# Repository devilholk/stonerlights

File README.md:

stonerlights
============

This project aims to control a bunch of (so far) local RGB LED's and other LED related devices.

This project is recently started and it puzzled together from old learning experiences so for now the structure is not the best.
Some parts may have separate licenses, I have not yet examined those legal details, if this applies it is stated in those files.

Be patient

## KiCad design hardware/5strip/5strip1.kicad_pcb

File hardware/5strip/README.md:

== Att göra ==

* Fixa till kretskortet så det uppfyller följande kriterier
** Klarar massa ström
** Har tillräckligt med C
** Kan prata RS-485 i halv duplex
** Kan prata USB
** Kan monitora matningsspänning som kan vara separat från 12 volt ifall en extern switch används

* Om tid finnes
** Stöd för kondensatormikrofron

== Notera ==

Förmodligen kommer man bara kunna använda en UART, kanske måste göra något fiffigt för att kunna använda båda vettigt, t.ex. multiplexa UART.

Detta dokumentet är ihophaffsat.

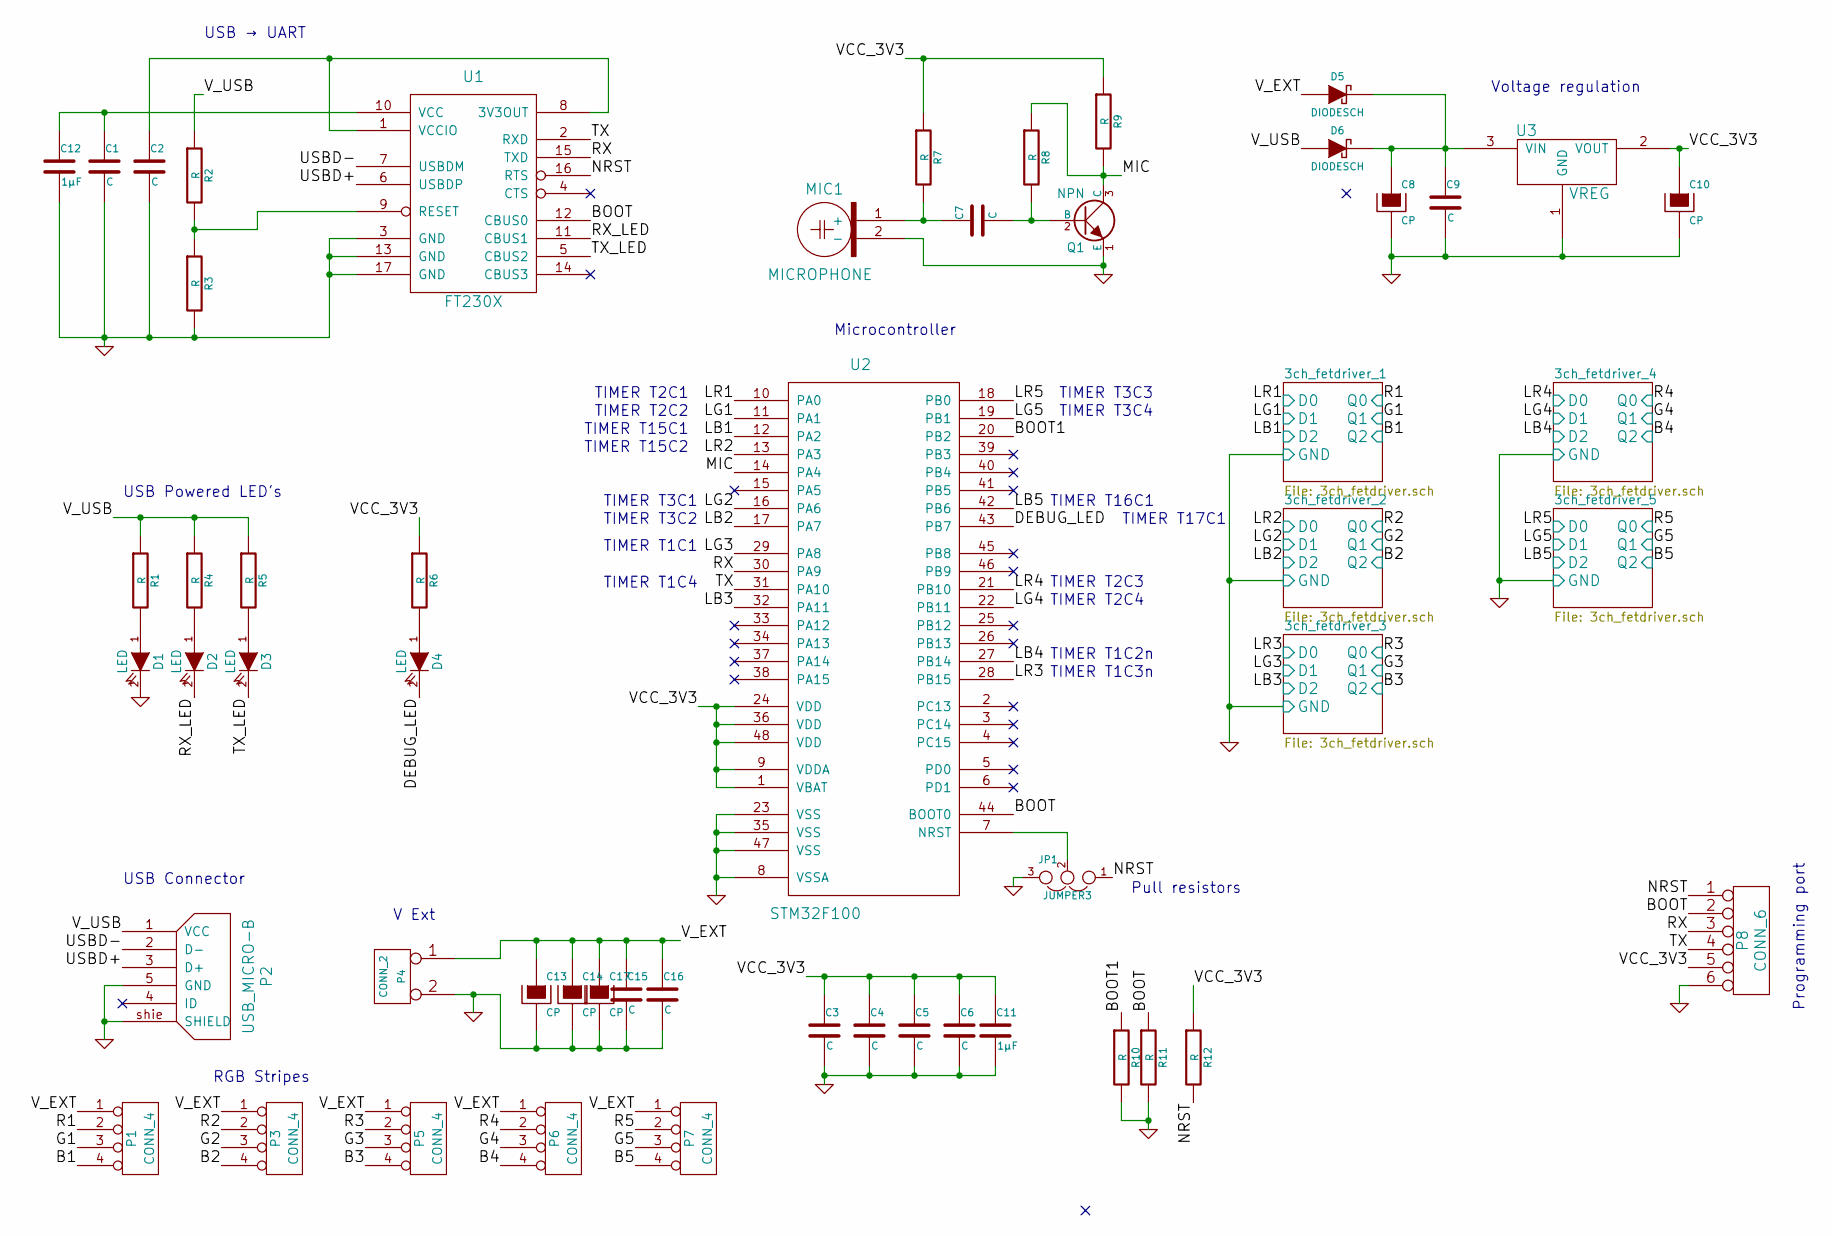
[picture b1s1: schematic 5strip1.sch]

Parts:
C1, C2, C3, C4, C5, C6, C7, C9, C15, C16: C
C8, C10, C13, C14, C17: CP
C11, C12: 1µF
D1, D2, D3, D4: LED
D5, D6: DIODESCH
JP1: JUMPER3
MIC1: MICROPHONE
P1, P3, P5, P6, P7: CONN_4
P2: USB_MICRO-B
P4: CONN_2
P8: CONN_6
Q1: NPN
R1, R2, R3, R4, R5, R6, R7, R8, R9, R10, R11, R12: R
U1: FT230X
U2: STM32F100
U3: VREG

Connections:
/3ch_fetdriver_1/D0: U2.10 (PA0); also elsewhere on the board
/3ch_fetdriver_1/D1: U2.11 (PA1); also elsewhere on the board
/3ch_fetdriver_1/D2: U2.12 (PA2); also elsewhere on the board
/3ch_fetdriver_1/Q0: P1.2; also elsewhere on the board
/3ch_fetdriver_1/Q1: P1.3; also elsewhere on the board
/3ch_fetdriver_1/Q2: P1.4; also elsewhere on the board
/3ch_fetdriver_2/D0: U2.13 (PA3); also elsewhere on the board
/3ch_fetdriver_2/D1: U2.16 (PA6); also elsewhere on the board
/3ch_fetdriver_2/D2: U2.17 (PA7); also elsewhere on the board
/3ch_fetdriver_2/Q0: P3.2; also elsewhere on the board
/3ch_fetdriver_2/Q1: P3.3; also elsewhere on the board
/3ch_fetdriver_2/Q2: P3.4; also elsewhere on the board
/3ch_fetdriver_3/D0: U2.28 (PB15); also elsewhere on the board
/3ch_fetdriver_3/D1: U2.29 (PA8); also elsewhere on the board
/3ch_fetdriver_3/D2: U2.32 (PA11); also elsewhere on the board
/3ch_fetdriver_3/Q0: P5.2; also elsewhere on the board
/3ch_fetdriver_3/Q1: P5.3; also elsewhere on the board
/3ch_fetdriver_3/Q2: P5.4; also elsewhere on the board
/3ch_fetdriver_4/D0: U2.21 (PB10); also elsewhere on the board
/3ch_fetdriver_4/D1: U2.22 (PB11); also elsewhere on the board
/3ch_fetdriver_4/D2: U2.27 (PB14); also elsewhere on the board
/3ch_fetdriver_4/Q0: P6.2; also elsewhere on the board
/3ch_fetdriver_4/Q1: P6.3; also elsewhere on the board
/3ch_fetdriver_4/Q2: P6.4; also elsewhere on the board
/3ch_fetdriver_5/D0: U2.18 (PB0); also elsewhere on the board
/3ch_fetdriver_5/D1: U2.19 (PB1); also elsewhere on the board
/3ch_fetdriver_5/D2: U2.42 (PB6); also elsewhere on the board
/3ch_fetdriver_5/Q0: P7.2; also elsewhere on the board
/3ch_fetdriver_5/Q1: P7.3; also elsewhere on the board
/3ch_fetdriver_5/Q2: P7.4; also elsewhere on the board
/BOOT: P8.2, R11.1, U1.12 (CBUS0), U2.44 (BOOT0)
/BOOT1: R10.1, U2.20 (PB2)
/DEBUG_LED: D4.2 (K), U2.43 (PB7)
/MIC: Q1.3 (C), R8.1, R9.2, U2.14 (PA4)
/NRST: JP1.1, P8.1, R12.2, U1.16 (RTS)
/RX: P8.3, U1.15 (TXD), U2.30 (PA9)
/RX_LED: D2.2 (K), U1.11 (CBUS1)
/TX: P8.4, U1.2 (RXD), U2.31 (PA10)
/TX_LED: D3.2 (K), U1.5 (CBUS2)
/USBD+: P2.3 (D+), U1.6 (USBDP)
/USBD-: P2.2 (D-), U1.7 (USBDM)
/VCC_3V3: C3.1, C4.1, C5.1, C6.1, C10.1, C11.1, P8.5, R6.1, R7.1, R9.1, R12.1, U2.1 (VBAT), U2.9 (VDDA), U2.24 (VDD), U2.36 (VDD), U2.48 (VDD), U3.2 (VOUT), U3.4
/V_EXT: C13.1, C14.1, C15.1, C16.1, C17.1, D5.1 (A), P1.1, P3.1, P4.1, P5.1, P6.1, P7.1
/V_USB: D6.1 (A), P2.1 (VCC), R1.1, R2.1, R4.1, R5.1
GND: C1.2, C2.2, C3.2, C4.2, C5.2, C6.2, C8.2, C9.2, C10.2, C11.2, C12.2, C13.2, C14.2, C15.2, C16.2, C17.2, D1.2 (K), JP1.3, MIC1.2 (-), P2.5 (GND), P2.shie (SHIELD), P4.2 (PM), P8.6, Q1.1 (E), R3.2, R10.2, R11.2, U1.3 (GND), U1.13 (GND), U1.17 (GND), U2.8 (VSSA), U2.23 (VSS), U2.35 (VSS), U2.47 (VSS), U3.1 (GND); also elsewhere on the board
unnamed: C2.1, U1.1 (VCCIO), U1.8 (3V3OUT)
unnamed: JP1.2, U2.7 (NRST)
unnamed: R2.2, R3.1, U1.9 (RESET)
unnamed: C1.1, C12.1, U1.10 (VCC)
unnamed: C8.1, C9.1, D5.2 (K), D6.2 (K), U3.3 (VIN)
unnamed: C7.2, Q1.2 (B), R8.2
unnamed: C7.1, MIC1.1 (+), R7.2
unnamed: D4.1 (A), R6.2
unnamed: D2.1 (A), R4.2
unnamed: D1.1 (A), R1.2
unnamed: D3.1 (A), R5.2

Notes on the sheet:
USB Powered LED's
Pull resistors
Voltage regulation
USB Connector
Microcontroller
USB → UART
RGB Stripes
Programming port
V Ext
TIMER T3C4
TIMER T3C3
TIMER T2C2
TIMER T2C3
TIMER T2C4
TIMER T3C1
TIMER T3C2
TIMER T1C3n
TIMER T1C2n
TIMER T1C4
TIMER T1C1
TIMER T2C1
TIMER T16C1
TIMER T17C1
TIMER T15C1
TIMER T15C2

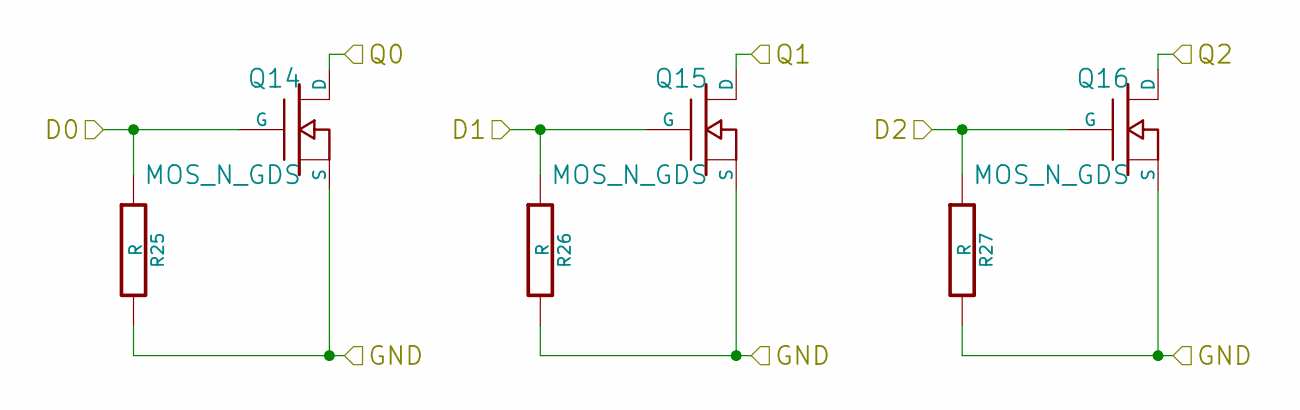
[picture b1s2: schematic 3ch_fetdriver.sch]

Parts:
Q2, Q3, Q4: MOS_N_GDS
R13, R14, R15: R

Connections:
/3ch_fetdriver_1/D0: Q2.1 (G), R13.1; also elsewhere on the board
/3ch_fetdriver_1/D1: Q3.1 (G), R14.1; also elsewhere on the board
/3ch_fetdriver_1/D2: Q4.1 (G), R15.1; also elsewhere on the board
/3ch_fetdriver_1/Q0: Q2.2 (D); also elsewhere on the board
/3ch_fetdriver_1/Q1: Q3.2 (D); also elsewhere on the board
/3ch_fetdriver_1/Q2: Q4.2 (D); also elsewhere on the board
GND: Q2.3 (S), Q3.3 (S), Q4.3 (S), R13.2, R14.2, R15.2; also elsewhere on the board

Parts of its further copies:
Q5, Q6, Q7, Q8, Q9, Q10, Q11, Q12, Q13, Q14, Q15, Q16: MOS_N_GDS
R16, R17, R18, R19, R20, R21, R22, R23, R24, R25, R26, R27: R

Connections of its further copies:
/3ch_fetdriver_2/D0: Q5.1 (G), R16.1; also elsewhere on the board
/3ch_fetdriver_2/D1: Q6.1 (G), R17.1; also elsewhere on the board
/3ch_fetdriver_2/D2: Q7.1 (G), R18.1; also elsewhere on the board
/3ch_fetdriver_2/Q0: Q5.2 (D); also elsewhere on the board
/3ch_fetdriver_2/Q1: Q6.2 (D); also elsewhere on the board
/3ch_fetdriver_2/Q2: Q7.2 (D); also elsewhere on the board
/3ch_fetdriver_3/D0: Q8.1 (G), R19.1; also elsewhere on the board
/3ch_fetdriver_3/D1: Q9.1 (G), R20.1; also elsewhere on the board
/3ch_fetdriver_3/D2: Q10.1 (G), R21.1; also elsewhere on the board
/3ch_fetdriver_3/Q0: Q8.2 (D); also elsewhere on the board
/3ch_fetdriver_3/Q1: Q9.2 (D); also elsewhere on the board
/3ch_fetdriver_3/Q2: Q10.2 (D); also elsewhere on the board
/3ch_fetdriver_4/D0: Q11.1 (G), R22.1; also elsewhere on the board
/3ch_fetdriver_4/D1: Q12.1 (G), R23.1; also elsewhere on the board
/3ch_fetdriver_4/D2: Q13.1 (G), R24.1; also elsewhere on the board
/3ch_fetdriver_4/Q0: Q11.2 (D); also elsewhere on the board
/3ch_fetdriver_4/Q1: Q12.2 (D); also elsewhere on the board
/3ch_fetdriver_4/Q2: Q13.2 (D); also elsewhere on the board
/3ch_fetdriver_5/D0: Q14.1 (G), R25.1; also elsewhere on the board
/3ch_fetdriver_5/D1: Q15.1 (G), R26.1; also elsewhere on the board
/3ch_fetdriver_5/D2: Q16.1 (G), R27.1; also elsewhere on the board
/3ch_fetdriver_5/Q0: Q14.2 (D); also elsewhere on the board
/3ch_fetdriver_5/Q1: Q15.2 (D); also elsewhere on the board
/3ch_fetdriver_5/Q2: Q16.2 (D); also elsewhere on the board
GND: Q5.3 (S), Q6.3 (S), Q7.3 (S), Q8.3 (S), Q9.3 (S), Q10.3 (S), Q11.3 (S), Q12.3 (S), Q13.3 (S), Q14.3 (S), Q15.3 (S), Q16.3 (S), R16.2, R17.2, R18.2, R19.2, R20.2, R21.2, R22.2, R23.2, R24.2, R25.2, R26.2, R27.2; also elsewhere on the board

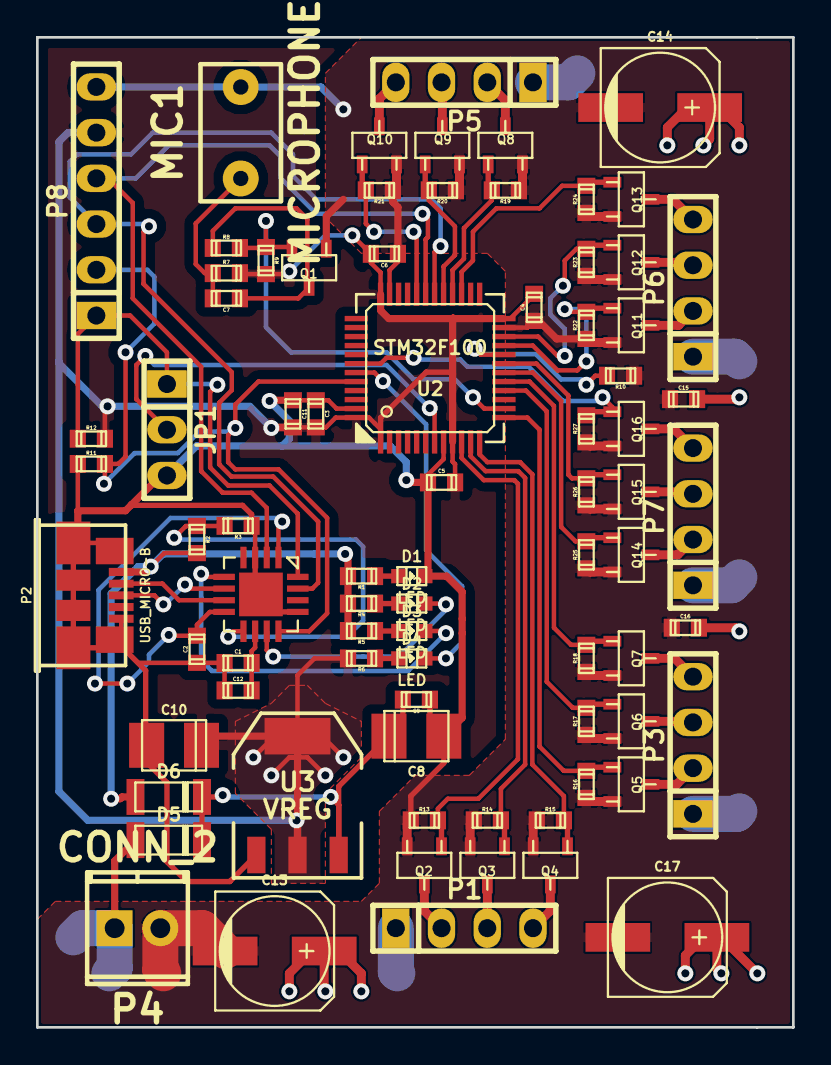
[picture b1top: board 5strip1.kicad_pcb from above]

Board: 2 copper layers, 42.0 x 55.0 mm, 79 parts (0 on the bottom side), 56 nets.

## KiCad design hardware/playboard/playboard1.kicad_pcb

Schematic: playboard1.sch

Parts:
C1, C2, C3, C4, C5, C6, C7, C11, C15: 100 nF
C8: 2.2 µF
C9, C14: 10 µF
C10: 10 nF
C12: 100 µF
C13: 22 µF
D1, D6: Red
D2: Green
D3, D4: DIODESCH
D5: Orange
D7: Pink
H1: DRV8833
J1: SMA
JP1, JP2: JUMPER3
JP3, JP4, JP5: JUMPER
MIC1: MICROPHONE
P1, P5: CONN_6
P2, P3: CONN_2
P4, P6, P8, P9, P10: CONN_4
P7: USB_MICRO-B
Q1, Q2: NPN
R1, R2, R3, R4, R6, R7, R9, R10, R11, R13: 10 kΩ
R5, R8: 4.7 kΩ
R12, R37, R38: 100 kΩ
R14, R15, R16: 290 Ω
R17: 1 kΩ
R18: 120 Ω
U1: FT232R
U2: STM32F100
U3: VREG
U7: RF2400-NANO

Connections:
/3ch_fetdriver_1/D0: U2.26 (PB13); also elsewhere on the board
/3ch_fetdriver_1/D1: U2.27 (PB14); also elsewhere on the board
/3ch_fetdriver_1/D2: U2.28 (PB15); also elsewhere on the board
/3ch_fetdriver_1/Q0: P6.2; also elsewhere on the board
/3ch_fetdriver_2/D0: U2.10 (PA0); also elsewhere on the board
/3ch_fetdriver_2/D1: U2.11 (PA1); also elsewhere on the board
/3ch_fetdriver_2/D2: U2.16 (PA6); also elsewhere on the board
/3ch_fetdriver_2/Q0: P8.2; also elsewhere on the board
/3ch_fetdriver_3/D0: U2.17 (PA7); also elsewhere on the board
/3ch_fetdriver_3/D1: U2.18 (PB0); also elsewhere on the board
/3ch_fetdriver_3/D2: U2.19 (PB1); also elsewhere on the board
/3ch_fetdriver_3/Q0: P9.2; also elsewhere on the board
/BOOT: P5.2, R3.1, U1.31 (DTR), U2.44 (BOOT0)
/BOOT1: R2.1, U2.20 (PB2)
/Board_NRST: JP2.2, U2.7 (NRST)
/DRV_VINT: C8.2, H1.14
/DRV_nFault: H1.8, U2.46 (PB9)
/DRV_nSLEEP: H1.1, R1.1, U2.21 (PB10)
/Debug_LED: D7.2 (K), U2.45 (PB8)
/I2C_EXTPULL: JP1.1, P10.1
/I2C_PULL: JP1.2, R7.1, R9.1
/MIC: C15.2, R37.2, R38.1, U2.14 (PA4)
/NRST: JP2.1, P5.1, R4.2, U1.32 (RTS)
/PO_H: H1.9, H1.16, Q1.3 (C), R10.2
/PO_L: H1.10, H1.15, P4.3, R8.1, U2.12 (PA2)
/RX: P5.3, U1.2 (RXD), U2.30 (PA9)
/RX2: P4.2, U2.13 (PA3)
/RX_LED: D2.2 (K), U1.21 (CBUS1)
/R_CE: U2.25 (PB12), U7.3
/R_IRQ: U2.22 (PB11), U7.8
/R_MISO: U2.40 (PB4), U7.7
/R_MOSI: U2.41 (PB5), U7.6
/R_NSS: U2.38 (PA15), U7.4
/R_SCK: U2.39 (PB3), U7.5
/SCL: P10.2, R7.2, U2.42 (PB6)
/SDA: P10.3, R9.2, U2.43 (PB7)
/TX: P5.4, U1.30 (TXD), U2.31 (PA10)
/TX_LED: D5.2 (K), U1.22 (CBUS0)
/USBD+: P7.3 (D+), U1.14 (USBDP)
/USBD-: P7.2 (D-), U1.15 (USBDM)
/VCC_3V3: C3.1, C4.1, C5.1, C6.1, C13.1, C14.1, JP1.3, P4.1, P5.5, R4.1, R10.1, R11.1, R13.1, R18.1, R37.1, U2.1 (VBAT), U2.9 (VDDA), U2.24 (VDD), U2.36 (VDD), U2.48 (VDD), U3.2 (VOUT), U3.4, U7.2
/V_EXT: C9.2, C10.2, D3.1 (A), H1.12, JP3.2, JP4.2, JP5.2, P3.1, P6.1, P8.1, P9.1, R17.1
/V_USB: C1.1, D4.1 (A), P7.1 (VCC), R5.1, R14.1, R15.1, R16.1, U1.19 (VCC)
/rgbled_1/B: P6.4; also elsewhere on the board
/rgbled_1/CA: JP3.1; also elsewhere on the board
/rgbled_1/G: P6.3; also elsewhere on the board
/rgbled_2/B: P8.4; also elsewhere on the board
/rgbled_2/CA: JP4.1; also elsewhere on the board
/rgbled_2/G: P8.3; also elsewhere on the board
/rgbled_3/B: P9.4; also elsewhere on the board
/rgbled_3/CA: JP5.1; also elsewhere on the board
/rgbled_3/G: P9.3; also elsewhere on the board
GND: C1.2, C2.2, C3.2, C4.2, C5.2, C6.2, C8.1, C9.1, C11.2, C12.2, C13.2, C14.2, D1.2 (K), D6.2 (K), H1.3, H1.6, H1.13, H1.17, J1.2, J1.3, J1.4, J1.5, JP2.3, MIC1.2 (-), P3.2, P4.4, P5.6, P7.5 (GND), P7.S, P7.shie (SHIELD), P10.4, Q1.1 (E), Q2.1 (E), R1.2, R2.2, R3.2, R6.2, R38.2, U1.4 (GND), U1.17 (GND), U1.20 (GND), U1.24 (AGND), U1.26 (TEST), U1.33, U2.8 (VSSA), U2.23 (VSS), U2.35 (VSS), U2.47 (VSS), U3.1 (GND), U7.1, U7.9, U7.11; also elsewhere on the board
unnamed: R5.2, R6.1, U1.18 (RESET)
unnamed: C2.1, U1.1 (VCCIO), U1.16 (3V3OUT)
unnamed: D7.1 (A), R18.2
unnamed: C15.1, Q2.3 (C), R12.1, R13.2
unnamed: C10.1, H1.11
unnamed: H1.2, H1.7, P2.1
unnamed: H1.4, H1.5, P2.2
unnamed: P1.1, U2.15 (PA5)
unnamed: J1.1, U7.10
unnamed: P1.6, U2.29 (PA8)
unnamed: P1.3, U2.33 (PA12)
unnamed: P1.2, U2.32 (PA11)
unnamed: P1.4, U2.34 (PA13)
unnamed: P1.5, U2.37 (PA14)
unnamed: C11.1, C12.1, D3.2 (K), D4.2 (K), U3.3 (VIN)
unnamed: C7.1, MIC1.1 (+), R11.2
unnamed: C7.2, Q2.2 (B), R12.2
unnamed: D5.1 (A), R16.2
unnamed: D1.1 (A), R14.2
unnamed: D2.1 (A), R15.2
unnamed: D6.1 (A), R17.2
unnamed: Q1.2 (B), R8.2

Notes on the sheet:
USB Powered LED's
Pull resistors
Voltage regulation
USB Connector
Microcontroller
USB → UART
RGB Stripes
GPIO

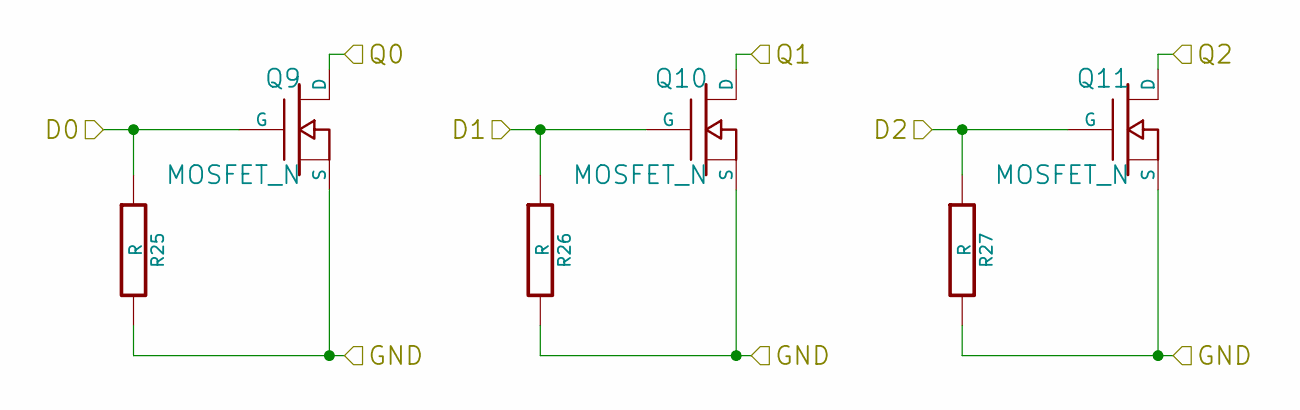
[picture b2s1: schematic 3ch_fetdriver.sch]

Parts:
Q3, Q4, Q5: MOSFET_N
R19, R20, R21: R

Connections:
/3ch_fetdriver_1/D0: Q3.G, R19.1; also elsewhere on the board
/3ch_fetdriver_1/D1: Q4.G, R20.1; also elsewhere on the board
/3ch_fetdriver_1/D2: Q5.G, R21.1; also elsewhere on the board
/3ch_fetdriver_1/Q0: Q3.D; also elsewhere on the board
/rgbled_1/B: Q5.D; also elsewhere on the board
/rgbled_1/G: Q4.D; also elsewhere on the board
GND: Q3.S, Q4.S, Q5.S, R19.2, R20.2, R21.2; also elsewhere on the board

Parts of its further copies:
Q6, Q7, Q8, Q9, Q10, Q11: MOSFET_N
R22, R23, R24, R25, R26, R27: R

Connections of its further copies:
/3ch_fetdriver_2/D0: Q6.G, R22.1; also elsewhere on the board
/3ch_fetdriver_2/D1: Q7.G, R23.1; also elsewhere on the board
/3ch_fetdriver_2/D2: Q8.G, R24.1; also elsewhere on the board
/3ch_fetdriver_2/Q0: Q6.D; also elsewhere on the board
/3ch_fetdriver_3/D0: Q9.G, R25.1; also elsewhere on the board
/3ch_fetdriver_3/D1: Q10.G, R26.1; also elsewhere on the board
/3ch_fetdriver_3/D2: Q11.G, R27.1; also elsewhere on the board
/3ch_fetdriver_3/Q0: Q9.D; also elsewhere on the board
/rgbled_2/B: Q8.D; also elsewhere on the board
/rgbled_2/G: Q7.D; also elsewhere on the board
/rgbled_3/B: Q11.D; also elsewhere on the board
/rgbled_3/G: Q10.D; also elsewhere on the board
GND: Q6.S, Q7.S, Q8.S, Q9.S, Q10.S, Q11.S, R22.2, R23.2, R24.2, R25.2, R26.2, R27.2; also elsewhere on the board

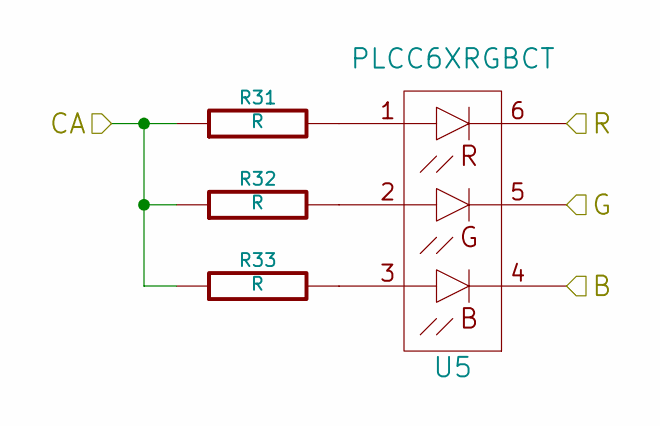
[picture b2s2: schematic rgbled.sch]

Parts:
R28, R29, R30: R
U4: PLCC6XRGBCT

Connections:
/3ch_fetdriver_1/Q0: U4.6 (R-); also elsewhere on the board
/rgbled_1/B: U4.4 (B-); also elsewhere on the board
/rgbled_1/CA: R28.1, R29.1, R30.1; also elsewhere on the board
/rgbled_1/G: U4.5 (G-); also elsewhere on the board
unnamed: R30.2, U4.3 (B+)
unnamed: R29.2, U4.2 (G+)
unnamed: R28.2, U4.1 (R+)

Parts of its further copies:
R31, R32, R33, R34, R35, R36: R
U5, U6: PLCC6XRGBCT

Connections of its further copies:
/3ch_fetdriver_2/Q0: U5.6 (R-); also elsewhere on the board
/3ch_fetdriver_3/Q0: U6.6 (R-); also elsewhere on the board
/rgbled_2/B: U5.4 (B-); also elsewhere on the board
/rgbled_2/CA: R31.1, R32.1, R33.1; also elsewhere on the board
/rgbled_2/G: U5.5 (G-); also elsewhere on the board
/rgbled_3/B: U6.4 (B-); also elsewhere on the board
/rgbled_3/CA: R34.1, R35.1, R36.1; also elsewhere on the board
/rgbled_3/G: U6.5 (G-); also elsewhere on the board
unnamed: R33.2, U5.3 (B+)
unnamed: R32.2, U5.2 (G+)
unnamed: R31.2, U5.1 (R+)
unnamed: R36.2, U6.3 (B+)
unnamed: R35.2, U6.2 (G+)
unnamed: R34.2, U6.1 (R+)

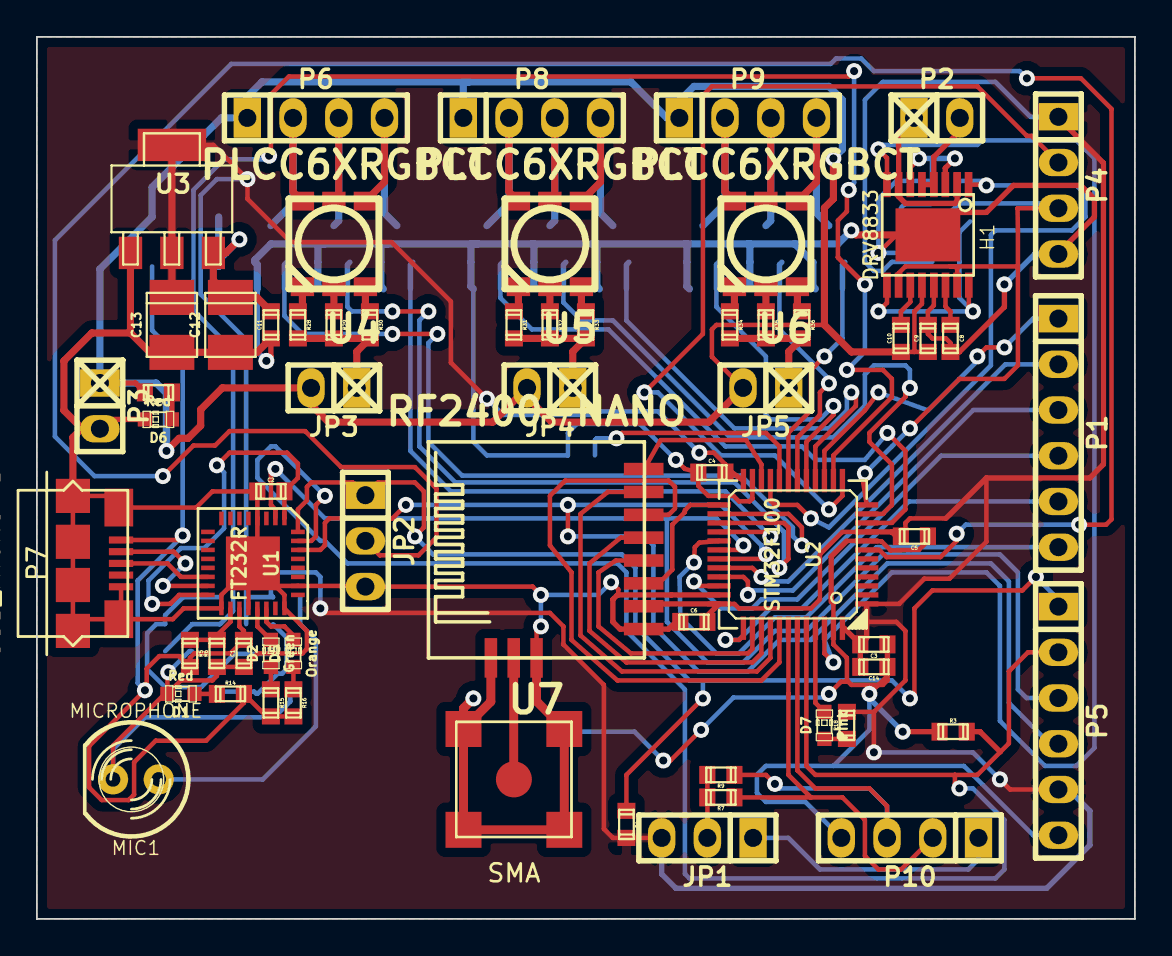
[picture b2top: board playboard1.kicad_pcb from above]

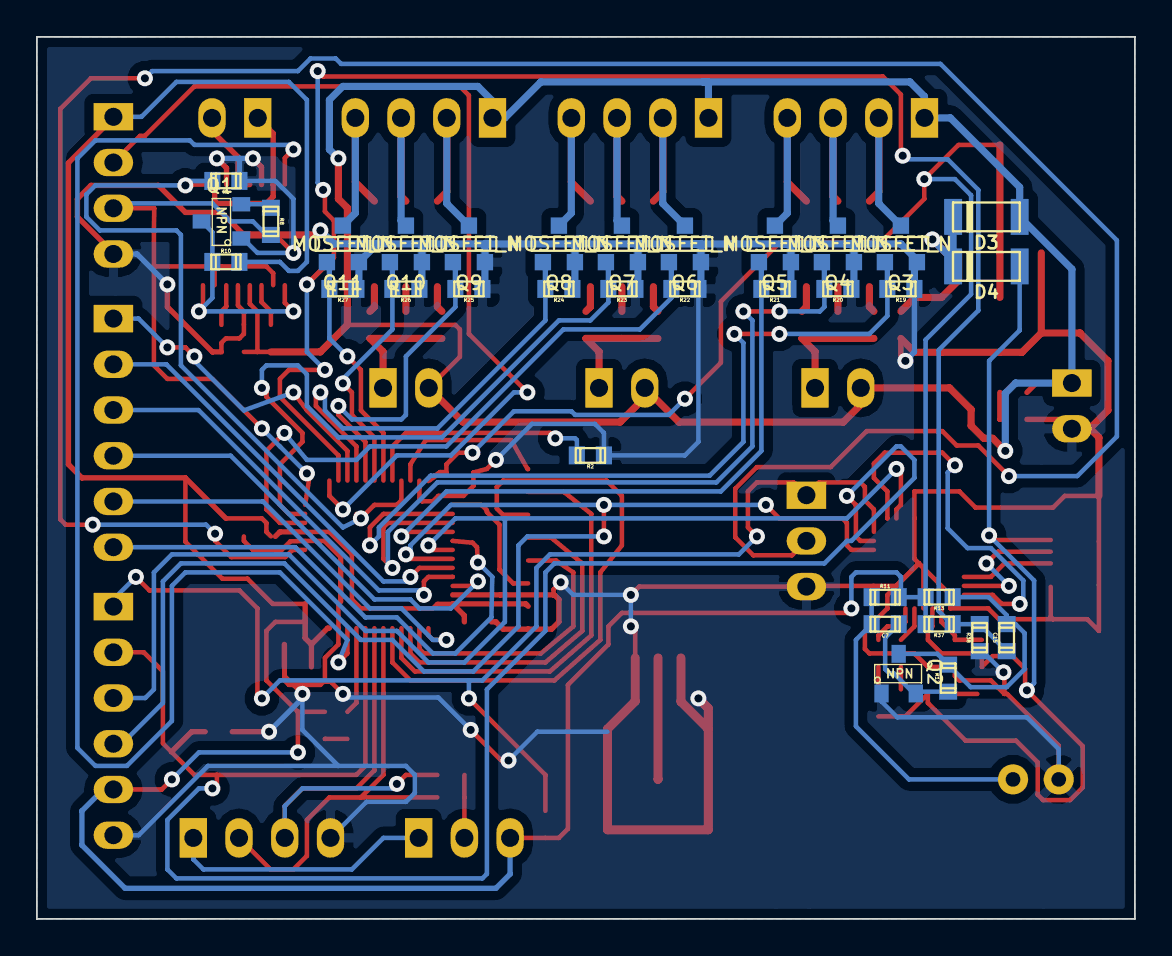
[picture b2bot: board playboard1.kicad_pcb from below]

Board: 2 copper layers, 61.0 x 49.0 mm, 96 parts (33 on the bottom side), 84 nets.

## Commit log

2013-03-21 Added some of my old code to the project
2013-03-21 Added some more old code from another computer that was lying around
2013-03-21 Commit code to test on the lamp
2013-03-27 Committing code forgotten on the kabelstegeslampa
2013-03-29 Added the source code for one of the lamps but did some modifications to .cproject
2013-03-29 Added the schematics for one of the lamps called rxlamp
2013-03-29 Updated README file
2013-03-29 Updated README.md for rxlamp hardware design
2013-03-29 Added 3D renderings and etching masks for rxlamp hardware design
2013-03-29 Built hex-file for firmware
2013-03-29 Added pinheader for dumb mode, added OSHW logo.
2013-03-29 Updated 3D renderings
2013-03-29 Updated 3D rendering. Added them to the commit this time too.
2013-03-29 Added RF-module to rxlamp
2013-03-29 Added the last modifications to the commit >.<
2013-03-29 Updated 3D pictures
2013-03-30 Added zones and vias for thermal relief of AMS1117
2013-03-30 Updated SVG plots
2013-03-30 Removed thermal relief for thermal zones around regulator. Removed pads from when drawing RF connection
2013-03-30 Some more improvements to thermal issues around regulator
2013-03-30 Updated README.md and removed SVG's
2013-03-31 Added GP pin, drew modules for protection
2013-03-31 Added the forgotten modules >.<
2013-03-31 Made close-to-final adjustments. Change versioning system to version < 1 since this is beta it makes more sense.
2013-03-31 Updated 3D-renderings
2013-03-31 Fixed vital design error and updated pictures.
2013-04-05 Added support for data over power supply, still few minor things to route
2013-04-12 Routed final traces on rxlamp
2013-05-01 Normalized sizes of footprint reference
2013-05-10 Changed the tantalium capacitor footprint to a smaller one
2013-06-05 Fixed bug where POWER_DATA was not properly clamped. (Thanks Benjamin!) And added the open source hardware logo, this time it might stick!
2013-06-05 Forgot to commit few files.
2013-06-13 Partial commit of new hardware
2013-06-16 Worked some more on the playboard
2013-06-16 Comitting before rerouting
2013-06-16 Redesigned board for playboard.
2013-06-29 Added some new hardware, included some code objects forgotten locally.
2013-07-03 Upload schematic PDF
2013-07-03 Reuploaded file, this time with visible stuff
2013-07-03 Added some values to schematic
2013-07-04 Updated timer registers in rxlamp code
2013-07-11 Implemented few color models, code is still a mess though. Be patient please =)
2014-01-11 Added missing linker script Fixed absolute file references in makefile
2014-04-08 Lade till README.md
